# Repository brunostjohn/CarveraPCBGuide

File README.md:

# How to make double-sided PCBs at home with a Carvera (Air)

This is a super in-progress guide for doing this. There's probably many better ways to do this, this is just what's worked for me.

## Table of Contents

- [How to make double-sided PCBs at home with a Carvera (Air)](#how-to-make-double-sided-pcbs-at-home-with-a-carvera-air)
  - [Table of Contents](#table-of-contents)
- [Materials, Tools, and Software](#materials-tools-and-software)
  - [Software](#software)
  - [Materials](#materials)
  - [Tools](#tools)
- [Preparation](#preparation)
  - [Making a PCB-friendly wasteboard.](#making-a-pcb-friendly-wasteboard)
  - [Making sure copper chips aren't fucking with our mill quality.](#making-sure-copper-chips-arent-fucking-with-our-mill-quality)
- [Going from PCB to Gcode.](#going-from-pcb-to-gcode)
  - [Creating your PCB in KiCAD](#creating-your-pcb-in-kicad)
    - [Quick note about text](#quick-note-about-text)
    - [Board setup](#board-setup)
    - [Pre-export work](#pre-export-work)
    - [Actually exporting the damn thing.](#actually-exporting-the-damn-thing)
  - [Importing your PCB to FlatCAM.](#importing-your-pcb-to-flatcam)
    - [Aligning your sides](#aligning-your-sides)
  - [Adding alignment drills.](#adding-alignment-drills)
  - [Actually making gcode for the align drills.](#actually-making-gcode-for-the-align-drills)
    - [Generating g-code for the front side of the PCB.](#generating-g-code-for-the-front-side-of-the-pcb)
  - [Generating g-code for the back side of the PCB.](#generating-g-code-for-the-back-side-of-the-pcb)
  - [Generating gcode for removing the front solder mask.](#generating-gcode-for-removing-the-front-solder-mask)
  - [Generating the gcode for removing the back solder mask.](#generating-the-gcode-for-removing-the-back-solder-mask)
  - [Generating the gcode for lasering on the front silkscreen.](#generating-the-gcode-for-lasering-on-the-front-silkscreen)
  - [Generating the gcode for lasering on the back silkscreen.](#generating-the-gcode-for-lasering-on-the-back-silkscreen)
  - [Generating the gcode for drills and edge cuts.](#generating-the-gcode-for-drills-and-edge-cuts)
- [Milling the board, lasering the board, and other random side quests.](#milling-the-board-lasering-the-board-and-other-random-side-quests)
  - [Attaching the fixture \& adding the fan.](#attaching-the-fixture--adding-the-fan)
  - [Attaching the PCB.](#attaching-the-pcb)
  - [Finding the 0 point and setting up work coordinates.](#finding-the-0-point-and-setting-up-work-coordinates)
  - [Drilling alignment holes.](#drilling-alignment-holes)
  - [Front copper isolation.](#front-copper-isolation)
  - [Front non-copper clearing](#front-non-copper-clearing)
  - [Back copper isoltion \& NCC.](#back-copper-isoltion--ncc)
  - [Applying the back solder mask.](#applying-the-back-solder-mask)

# Materials, Tools, and Software

## Software

- KiCAD
- Makera's CAM
- Fusion 360
- FlatCAM

  This guide uses the 8.994 beta version of FlatCAM. There _will_ be differences between other versions, but the workflow should stay roughly the same.

## Materials

- Copper-clad FR4, duh.
- UV-curable solder mask (both in target solder mask colour and white, you'll see why).
- Some random ass wood for milling the PCB fixture. (should fit on the Carvera bed)
- TPU to make a spindle fan
- Double sided tape.
- An acetate sheet.

## Tools

- The Carvera Air.
- 3D printer (optional)
- A UV light.
- Shop vac (optional)
- The sanding block that came with the Carvera
- Carvera's Laser Module.
- A 0.2mm corn bit/endmill.
- A 2mm/4mm drill bit.
- Makera's solder mask removal bit.
- Corn bits in other various sizes.
- Drill bits also in other various sizes.
- Something to scrape the PCB off the fixture after the double sided tape. I'm using a 3D printer bed scraper.

# Preparation

## Making a PCB-friendly wasteboard.

The MDF wasteboard on the Carvera isn't super friendly to milling PCBs so we need to make our own thing to which we will attach PCBs. Fortunately enough, I've solved this problem already by making a Carvera friendly thing that can accomodate large-ish PCBs and screws into the bed. It isn't entirely my own creation, it's based on [this guide's](https://hackaday.io/project/202478/instructions) fixture created by [Vedran](https://hackaday.io/vedranMv). I only modified it to hold larger PCBs. You don't need to mill all the holes, it's really only the screwholes that matter. Here's a photo of mine.

I made it out of some random wood my landlord had in her shed. Just make if flat enough and you'll be fine.

You can get the [Fusion project here](./projects_and_gcode/fusion/PCB%20fixture%20thing.f3d) or the [STEP file here](./projects_and_gcode/step/PCB%20fixture%20thing.step).

## Making sure copper chips aren't fucking with our mill quality.

When the bit you're using mills it's own chips (or in this case, dust), you get more burrs and more bullshit. To prevent this you can either use a vaccuum attached to your Carvera or a delightful fan.

[RedGT500](https://www.printables.com/@RedGT500_1977691) has already made a great fix to this. A 3D printable fan made out of TPU that's made to go on your spindle. You can even see mine in that photo of the fixture above. You can download it [here](https://www.printables.com/model/1332188-carvera-spindle-fan-beefy-version/files). I've also reuploaded it [here](./projects_and_gcode/step/Spindle%20Fan.step) to protect against link rot.

# Going from PCB to Gcode.

## Creating your PCB in KiCAD

Teaching you to actually make PCBs is outside the scope of this guide. God knows I know fuck all about making PCBs or CNC. What I do know is how I made my PCB so that it works with this process.

This doesn't affect making your schematic, so I'm gonna skip right over to the PCB editor.

### Quick note about text

First, if you think any text you make is gonna look fine, you're sorely mistaken. Don't even bother. Hide all the text and make sure it doesn't end up in the final exports.

### Board setup

Let's move onto the money shot.

- The minimum clearance between tracks should be 0.2mm (you _can_ set 0.1mm and have good results but you have to mind yourself so you don't get the tracks too close together, this is relevant for some smaller ICs or USB-C ports).
- The minimum track width should be 0.2mm (NOT any lower unless you have tiny ass bits, which I don't and haven't tested).
- Your minimum via diameter should be 0.9mm (so that you can drill 0.6mm holes for them). Smaller vias will be a pain in the ass, don't even bother with them.
- Your copper to hole clearance should be 0.25mm. You can go lower (as low as 0.2mm), but I wouldn't recommend it.
- Your copper to edge clearance should be 0mm. This way KiCAD won't force FlatCAM to mill the shit out of the boards edges wasting your time and bit life.
- Your minimum through-hole should be 0.3mm (or the smallest bit you've got).
- Your hole to hole clearance should be 0.2-0.25mm.

### Pre-export work

To make our board show up consistently in the right spot in all of the pieces of software we'll be using, you gotta set a grid & drill/place origin.

In KiCAD's PCB editor, select the `Grid Origin` option.

Then, place it at the bottom left corner of your board.

Now, press and hold the grid origin button until a second option pops out.

That's the drill origin button. Click on that and place it in the same spot as the grid origin.

You are now ready to export your board.

### Actually exporting the damn thing.

Click on `File > Fabrication Outputs > Gerbers`.

Now, select the output folder, select your layers, select `Use drill/place file origin`. First, click on `Generate Drill Files` and also select `Drill Origin > Drill/place file origin`, then click on `Generate Drill File` and close. Then, click on `Plot`. Your board should now have the required outputs to be milled in the folder you selected.

(I've taken this photo from [Vedran's guide](https://hackaday.io/project/202478/instructions) because I'm on macOS Tahoe and KiCAD's export window is freaking OUT on it)

You should now have the Gerbers you need to mill your board.

## Importing your PCB to FlatCAM.

Open up FlatCAM and click on `File`. Then hover over `Open` and select `Open Gerber`. **ONLY** import your front and back copper layers. Don't import anything else.

You should see your board on the newly opened side panel:

To make seeing them a little bit easier, feel free to select whatever colours you think they should have:

Having done that, you should see something like this:

### Aligning your sides

It may seem like the boards are in the right orientation, but that is not the case. Remember, this is a 2D program and if you flip over the board, you will notice that it's almost as if it's _mirrored_. Let's fix that.

At the top of the UI, click on `Tool` and select `2-Sided PCB`:

This will take you to a panel that looks something like this:

First, as the source object, select the _back side of the board_. I know that that's confusing, but this is the object that will end up getting mirrored. Horrible naming, but we can work with that.

Let's now mirror our back side. in the Mirror Operation section of the 2-Sided PCB panel, select the X axis for your mirror operation (we'll be flipping the board over on its long side) and select Box as your reference. I've seen a YouTuber use Point and do some crazy ass math, but that's quite silly considering we're on a computer that can _compute_ it for us.

Next, as your reference object, select the front side of your board. If you've done this right, your Mirror Operation panel should look something like this:

Looks great! Let's press Mirror to get it onto the right side. Things will feel a bit wrong now. If you've done this right, this is what it should look like:

This seems wrong because our vias are not aligned. Remember, this is _Flat_ CAM. So what is happening here instead is that we're looking at our boards from the _top_, just like our CNC will. This means that if you physically flip over your soon-to-be board, you will see the same view as you are right now in FlatCAM.

## Adding alignment drills.

We're almost done with the 2-Sided PCB tool. All we need to do now, is make sure that we can somehow reliably align both sides on our CNC's work area. If you've ever done this manually, you'll know that it's basically impossible.

In the PCB Alignment section, set your drill diameter to the size of your alignment pins. I'm using the 2mm diameter dowel pins that came with the PCB fabrication toolkit, but you can use 4mm if you haven't bought it and are using the slightly larger pins that come with the machine itself.

To do this accurately, we need to do some math.

Let's figure out where our alignment pins should be. Go back to the project tab in FlatCAM and find the front side of your board. Right click on it and select `Properties`.

In there, you will see a dimensions section. This contains what we're looking for, the **Length** and **Width** of the board:

Make note of these and go back to the 2-Sided PCB tool like shown before.

In the PCB Alignment section, there will be a text field titled `Alignment Drill Coordinates`. We're calculating these because it's gonna be hard to get this right manually.

We want 4 drills on opposite corners of the board 3mm away from the board itself.

So what we want is:

- **A hole on the bottom left.**
  In my case, it's at `(0.0, -3.0)` because we're to the leftmost corner of the board, 3mm away from the bottom edge.
- **A hole on the top left.**
  In my case, that's `(0.0, 25.669)` because I want it on the same "line" as the left edge but 4mm away from the top edge (so $22.669+3=25.669$).
- **A hole on the bottom right.**
  In my case, that's at `(51.024, -3)` because we're at the rightmost corner of the board, 3mm away from the bottom edge.
- **A hole on the top right.**
  For me, that's at `(51.024, 25.669)` because I want it on the same "line" as the right edge but 4mm away from the top edge (so $22.669+3=25.669$).

This, in aggregate, is:
```(0.0000, -3.0000),(51.0240,-3),(0, 25.6690),(51.0240,25.6690)```

Let's punch these numbers into FlatCAM and click on `Create Excellon Object`.

You should now see your alignment drills on the Plot Area.

## Actually making gcode for the align drills.

I don't trust FlatCAM with doing these drilling ops. Partly because I'm not super familiar with it and partly because MakeraCAM makes it dead easy. Let's open up a new 3-axis project in MakeraCAM.

Now, set up your stock. Pick the PCB material and set the XYZ values to anything that fits with your board.

Now we're ready to drill some shit. Let's export our fresh Excellon drills from FlatCAM.

Save them somewhere they won't get lost and get back to MakeraCAM. In the layer panel, right click 2D layers and select `Import Graphic > Import PCB`.

Once you import your drills, you should be able to see them in the layers panel and in the work area. Don't worry if the size is slightly wrong, that's okay.

You'll also notice that they go outside of the "work area". **Don't move them by even a millimetre**. Just leave them as-is. This is fine and will be rectified later when we go to drill them.

Select all your drills by using MakeraCAM's `Select Graphics` options:

You should see them all get kind of dashy. With them selected, go into 2D toolpaths and select 2D drilling.

Let's sort out the settings. I'm using my 2mm drill. I used a clearance height of 5mm because there's nothing in the way of the toolhead as these drills are being created. Use feeds & speeds for PCBs. Your wooden base and bit will be fine (I think?). We're drilling 6mm down because the dowel pins are about 10mm in height, and we want them to be secure.

That's it! You're now ready to drill your alignment drills. Let's move onto generating the gcode for our top and bottom layers.

### Generating g-code for the front side of the PCB.

Let's go back to FlatCAM. Double click on the front layer of your PCB. That should bring you to this panel:

We will start by electrically isolating your traces. This removes material around only the traces. Click on `Isolation Routing`. You will now see a different panel:

We will lie about our bits diameter. This is so that FlatCAM actually mills them. Your tool's supposed to be smaller than your traces. But it's fine if it's equal to their width. So fuck it, let's lie. It _does_ work. Double click what's currently in there and type in 0.19. This will make some of your traces slightly undersized. For me, that's worked out okay but YMMV. Then select the tool type. We're using a corn bit so any of the CX options are fine. Let's pick C1 for the vibes.

Now, right at the bottom, click on `Generate Geometry`. This will create geometry for us that we can later use to CNC the board.

You will see a bunch of toolpath parameters. In the path type, select `Iso`:

I'm setting my cut Z to -0.05. That's enough to get the copper off the board and get to the FR4 for me. Things might be different for you, so experimentation is king here. I'm using an XY feedrate of 120 and Z feedrate of 60. These tools are mad fragile so it's better to not fuck about. I'm also using a spindle speed of 15k because I've gotten the best results that way.

When you're done, click on `Generate CNCJob object`. This will generate actual gcode we can use. You will now see an actual toolpath forming. The panel will also give you an option to save your gcode. Do that and open the generated file in Notepad.

For the gcode-inclined among us, you'll notice that T1 and M6 are on separate lines:

This makes the Carvera very angry. It stops the job and loses its heightmap. It's a nice machine so let's not make it angry. Delete the newline between these, add a space, and save. Here's what a fixed file looks like:

You'll need to do this for every CNCJob you save from FlatCAM. There's probably a fix for this. I haven't found it yet.

Let's now get back to the Project tab in FlatCAM. Double click on your front layer again. This will open up the Gerber Object panel again. This time, click on NCC Tool. That is the **n**on-**c**opper **c**leaning tool. Once again select the C1 tool type and a diameter of 0.19. Generate your geometry. Now, sometimes, that takes ages. Let it cook. It might complain that it couldn't fully isolate.

Sometimes it might even tell you where the polygons it failed to clear are. Double check that everything is still fine. It probably is.

Once you do, configure your toolpath. Most, if not all, of the settings will be the same as for isolating traces.

Once you're satisfied, click on the `Generate CNCJob object button`. Verify your toolpath and save your CNC code. Repeat the same steps as for the isolation gcode where we had to remove a newline from there.

## Generating g-code for the back side of the PCB.

Repeat the steps you did for the front side, just for the back side this time.

We're now officialy done with FlatCAM. We don't need to look at it again (yay!).

## Generating gcode for removing the front solder mask.

Let's open up a new 3-axis project in MakeraCAM.

Now, set up your stock. Pick the PCB material and set the XYZ values to anything that fits with your board.

In the layer panel, right click 2D layers and select `Import Graphic > Import PCB`.

Select your _front copper layer_. I know you'll be tempted to use the solder mask gerber. Because the solder mask gerber won't remove mask from the vias, It's not particularly useful to us.

Once you import your layer, it should look something like this:

You'll notice MakeraCAM helpfully created a pad layer for us. That's what we'll be primarily working with. Let's hide the non-pad layer.

Right click on your pad layer and click on `Select graphics` to select all our pads & vias.

With that selected, select the 2D Pocket toolpath from the 2D options.

For this pocket, we are using the solder mask removal tool.

We're using a taller clearance height to avoid fucking the tool into our dowel pins. An end depth of 0.3mm has delivered solid results to me, but in the worst case one can re-run the toolpath with a higher depth. Anyways, let's run calculate.

Great! It seems like everything was calculated. Wait, not everything. Some of the pads are too small!

Don't worry, I have a trash quality solution to this that works unnecessarily well.

Start by holding down `Shift` and left clicking on pads that weren't generated. Group this by the _size of the pad_. So for example, I'm not gonna do the RP2040 pads because they're small as fuck. We'll start with the NOR flash:

Now, let's create a new pocket toolpath. Same settings as before with one change. We will use the offset option.

This will force MakeraCAM to generate a toolpath by making it pretend our selected graphic is larger than it actually is. This _does_ make pads slightly larger than they should be. But in reality, with our NCC toolpaths and solder mask spread, this usually means that the extra removed soldermask is still kind of there because it goes deeper than the tool does. You'll see that in a photo later.

Now, let's do the RP2040 pads (as an example of some smaller pads). let's start with the ones oriented horizontally. Do the same offset trick. Here's where it gets funky. These pads are small as shit so ripping them off is SUPER easy. You want to _minimise the amount of time the tool spends on the pad_. And also, you want to minimise the pad itself. So experiment until you find the smallest possible offset that makes the machine mill the pads.

This will take experimentation. Take your time with it. Do the same for the vertical pads now.

When you're done, your Carvera should have toolpaths for all your pads.

Export your gcode and save for later.

## Generating the gcode for removing the back solder mask.

Take your mirrored back board from FlatCAM and export the Gerber. Import to MakeraCAM and mirror it vertically:

## Generating the gcode for lasering on the front silkscreen.

Let's open up a new 3-axis project in MakeraCAM.

Now, set up your stock. Pick the PCB material and set the XYZ values to anything that fits with your board.

In the layer panel, right click 2D layers and select `Import Graphic > Import PCB`.

Import your front silkscreen layer.

Any text you have needs to go. I haven't figured out how to make it legible yet but it'll legitimately look like trash.

Just delete it.

Now, this part you can only do after experimenting a little bit. The laser is _very_ slightly off from where the mill ends up. This will cause your silkscreen to be off. I still haven't gotten the right offsets, but here's how to apply them.

Right click your silkscreen layer in the layers section of MakeraCAM and click on `Select Graphics`.

Now, click on the transform menu and select `Move`.

You will be brought to a delightful panel for moving shit. It'll tell you your current selection's location:

Now, my last proof board turned out like this:

It looks like on the X axis we are too far to the right (so, we need to compensate by subtracting) and on the Y axis we are too far to the bottom (so we need to compensate by adding).

I'm gonna try -0.75mm on the X axis and +0.3mm on the Y axis.

Based on the values in the move panel:

- X axis
  $24.579-0.75=23.829$
- Y axis
  $11.161+0.3=11.461$

Let's type that into MakeraCAM.

Great, with our paths translated we're ready to create our laser toolpaths.

Now, this is very important, **select things by their thickness**. Group things as thick as each other together. This way, you can get a result that doesn't look like shit.

In my case, there's only a few tiny bits that have the same thickness. Let's select everything else for now.

From the laser toolpaths dropdown, select Laser Vector.

As for settings, set speed at a hilariously low 30mm/min and power at 3%. We're not actually trying to engrave or cut anything (you'll see when we actually run the toolpaths), we're exploiting the laser's wavelength to use it to selectively cure the white soldermask. Set the indent distance at _the lowest possible value that still generates a complete toolpath_. Pair that with using the laser in line mode. The thinnest laser path can generate the thickest solder mask, so it's better to err on the cautious side.

Now, thing by thing generate your thicker paths with the appropriate indent distances. The thicker it is, the higher the indent distance should be.

With all the toolpaths done, you can now export your gcode and stash it for later.

## Generating the gcode for lasering on the back silkscreen.

About the same as the front silkscreen. Just with the caveat that you have to mirror it vertically as shown in the previous sections.

## Generating the gcode for drills and edge cuts.

This will be the last toolpath for our PCB.

Let's open up a new 3-axis project in MakeraCAM.

Now, set up your stock. Pick the PCB material and set the XYZ values to anything that fits with your board.

In the layer panel, right click 2D layers and select `Import Graphic > Import PCB`.

Import your PTH, NPTH, and edge cut layers.

For creating drill holes, there are 2 strategies. You can use a 2D Pocket toolpath or a 2D Drill toolpath. The drill toolpath is greatly preferred because it risks your pads less. If you don't have the right sized drills though, you can make do with a pocket and very often your PCB will be okay. We will use both strategies here because it's fun.

Let's start by using plain ol' drills. Right click the layer that has the right sized drills for your bits and click on `Select Graphics`.

Now, select the 2D Drilling toolpath from the 2D toolpaths dropdown.

As for the settings, you want to drill 1.6mm down to ensure you go fully through the board. This will make a delightful hole in your wooden block. That's fine because the bit should survive this blunder. Remember to use a drill that matches your layer drill size.

Now, let's do the pleb way of drilling a hole - the 2D pocket toolpath. Select the drills you don't have the proper bits for and select 2D Pocket from the 2D toolpaths dropdown.

Select a corn bit smaller than your smallest drill size. Make it mill 1.6mm down to make sure we get all of the board.

For the strategy, we're doing outside in. I've gotten the best results with that.

Almost done with our last toolpath! Let's cut the board out of the stock. Now, edge cuts are sneaky little shits. It doesn't look like it, but there's two of them. Zoom in and delete the smaller one.

Select your edge cut (NOT cuts!) and select the 2D Contour toolpath from the 2D toolpaths dropdown.

For these, use your _biggest_ corn bit. Otherwise, it'll look like shit. Again, cutting 1.6mm down.

To not end up fucking our board, pick the outside strategy.

Last one, so the board doesnt go flying out of the FR4, add some tabs. Click on custom, make them triangle shaped, and select `Add`.

Now, click roughly in the centre of each edge of the contour.

Sick. Now press `Exit Add` and calculate your toolpath.

You can now export your g-code. Since we're using many corn bits, MakeraCAM will complain about tool numbers. Change them up until you're happy with the numbers. Just make each tool have a different one.

With your g-code exported, you're now ready to mill some shit. Let's get to making everything.

# Milling the board, lasering the board, and other random side quests.

## Attaching the fixture & adding the fan.

Let's get started by screwing in the fixture and adding the fan. Take anything in the spindle out of the spindle and press fit the fan. After that, reference the photo below to see where the fixture screws in. Use the medium-long screws that come with the Carvera.

## Attaching the PCB.

Put double sided tape all over the back of the PCB.

Then, stick it on the fixture. Avoid putting any drills around the screws at the bottom of the fixture. Make sure there's enough space to flip the board over while keeping the entirety of it on the fixture itself.

Feel free to use the roller from the PCB fabrication kit (if you bought it) to ensure the adhesive is nice and squished.

## Finding the 0 point and setting up work coordinates.

Insert the leveling probe into the spindle.

Let's open up the Carvera Controller. Connect to the machine and click on the top right button. Then, select the device diagnose menu. In there, turn on the probe laser.

You will see the laser come alive. Now, exit the diagnose menu and go into the manual control menu.

Here, move the toolhead until the laser pointer is pointing at where you want the X and Y zero points to be (where the PCB starts). Remember that some of the align holes are at minus points when doing this. If you feel like things are moving too slow or too fast, change how fast the Carvera moves the axes.

Find your zero point.

Once you're happy with the zero point, let's start running the alignment hole job.

## Drilling alignment holes.

When you click on start job, you will see a work origin and leveling menu. Your toolhead is at the X and Y zero point right now. Let's let the machine know about that by clicking `Config` under `Set Work Origin` and setting the anchor as `Current Pos`.

Let's move onto leveling. You don't need to go super crazy here, the drills just need to be accurate enough.

Let's start our job and wait until it's done.

Okay, there's holes now! Get rid of the debris using a vacuum.

After you've cleared them, put the dowel pins in. From now on, **anytime you're machining the board the dowel pins should be in it**. That will prevent unnecessary movement and ensure alignment.

## Front copper isolation.

Let's move onto the fun stuff. Load up the copper isolation job.

**DO NOT** change the work origin settings. These will now stay the same for the entire duration of us milling this board.

We will change the levelling settings though. We want to be absolutely certain we have all the weird imperfections accounted for. Use 15 levelling points. Yeah, it's a lot. Yeah, it'll take ages. And yeah, it's worth it.

Great! Let's wait for our machine to be done.

Nice result!

## Front non-copper clearing

Let's now move onto milling out the non-copper sections. Load up the NCC job.

Now, before you run it, **DO NOT** enable any option that requires the probe. We want the Carvera to reuse it's heightmap. Doing that will cause it to clear it and you'll get worse results.

Let's wait for NCC to be done.

## Back copper isoltion & NCC.

With front NCC done, we can scrape the board off our fixture. Add double sided tape _only above and below the board_. If you add tape onto the board, you run the risk of scraping traces.

Just like with the front side, run maximum leveling (15 points) and start the isolation job. Once done, start NCC without using the probe. Once that's done, we're ready to move onto solder mask.

## Applying the back solder mask.

Right now, the board will have a bunch of burrs. We don't want that as it will cause an uneven stick & coat for the UV-curing solder mask. Fortunately, Makera includes a fine enough sanding block with the Carvera.

Rub that shit on the board until it gets nice and shiny.

Now, the sander itself leaves some nasty shit on the board. Grab some isopropanol and swab it off.

As you can see, that is quite nasty.

Okay, grab your favourite solder mask.

Apply it evenly-ish on the board.

Now, grab a transparent sheet. I'm using some random acetate sheets I had at home.

Squish it on the board.

Now, use the roller that comes in the PCB fabrication kit (or a credit card) to get the solder mask spread evenly (enough) on the board.

Once you're done, you should be left with something that looks kind of like this.

Now, grab your favourite UV light, set it to at least 15 minutes, and start curing this thing.

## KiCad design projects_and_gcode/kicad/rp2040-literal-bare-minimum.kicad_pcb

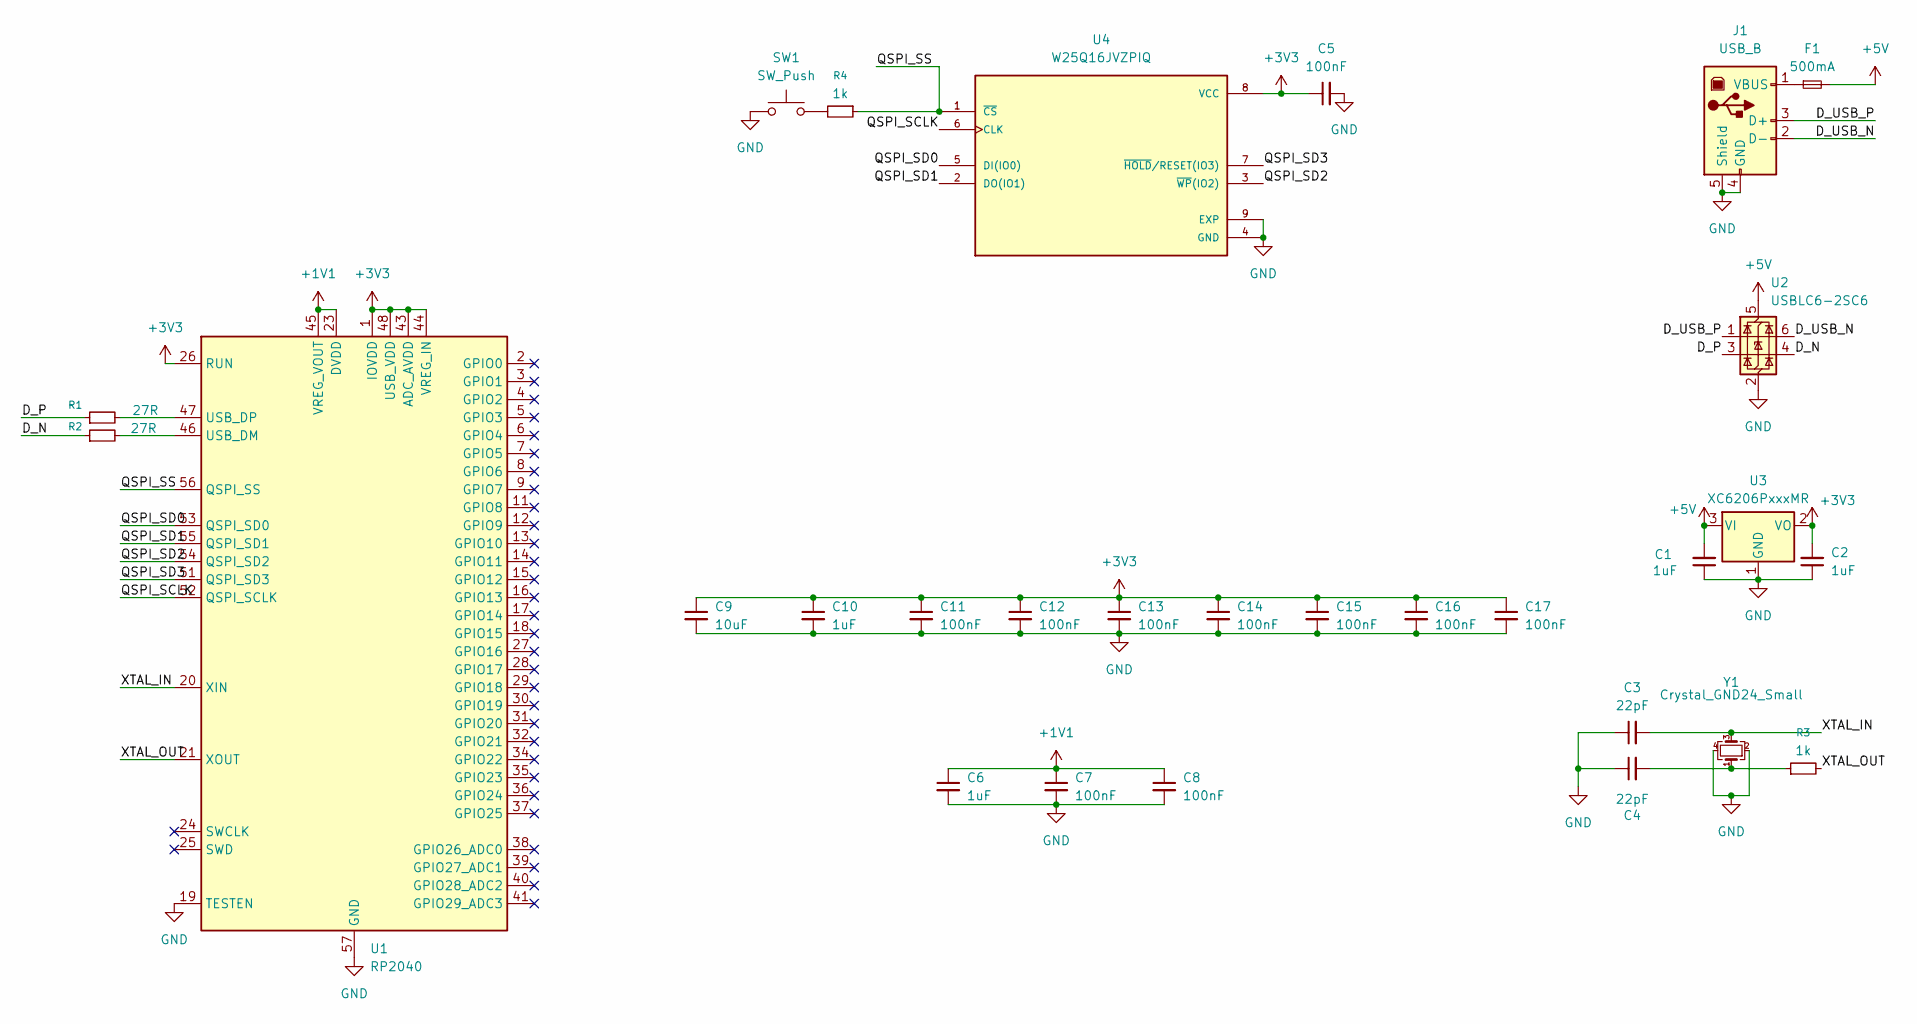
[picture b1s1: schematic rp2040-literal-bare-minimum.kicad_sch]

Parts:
C1, C2, C6, C10: 1uF; C_0402_1005Metric-notxt
C3, C4: 22pF; C_0402_1005Metric-notxt
C5, C7, C8, C11, C12, C13, C14, C15, C16, C17: 100nF; C_0402_1005Metric-notxt
C9: 10uF; C_0402_1005Metric-notxt
F1: 500mA; Fuse_1206_3216Metric-notxt
J1: USB_B; USB_B_Lumberg_2411_02_Horizontal-notxt
R1, R2: 27R; R_0402_1005Metric-notext
R3, R4: 1k; R_0402_1005Metric-notext
SW1: SW_Push; SW_SPST_EVQP2-notxt
U1: RP2040; QFN-56-1EP_7x7mm_P0.4mm_EP3.2x3.2mm
U2: USBLC6-2SC6; SOT-23-6
U3: XC6206PxxxMR; SOT-23-3
U4: W25Q16JVZPIQ; SON127P500X600X80-9N
Y1: Crystal_GND24_Small; Crystal_SMD_3225-4Pin_3.2x2.5mm-notxt

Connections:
+1V1: C6.1, C7.1, C8.1, U1.23 (DVDD), U1.45 (VREG_VOUT), U1.50 (DVDD)
+3V3: C2.2, C5.1, C9.1, C10.1, C11.1, C12.1, C13.1, C14.1, C15.1, C16.1, C17.1, U1.1 (IOVDD), U1.10 (IOVDD), U1.22 (IOVDD), U1.26 (RUN), U1.33 (IOVDD), U1.42 (IOVDD), U1.43 (ADC_AVDD), U1.44 (VREG_IN), U1.48 (USB_VDD), U1.49 (IOVDD), U3.2 (VO), U4.8 (VCC)
+5V: C1.2, F1.2, U2.5 (VBUS), U3.3 (VI)
/D_N: R2.1, U2.4 (I/O2)
/D_P: R1.1, U2.3 (I/O2)
/D_USB_N: J1.2 (D-), U2.6 (I/O1)
/D_USB_P: J1.3 (D+), U2.1 (I/O1)
/QSPI_SCLK: U1.52 (QSPI_SCLK), U4.6 (CLK)
/QSPI_SD0: U1.53 (QSPI_SD0), U4.5 (DI(IO0))
/QSPI_SD1: U1.55 (QSPI_SD1), U4.2 (DO(IO1))
/QSPI_SD2: U1.54 (QSPI_SD2), U4.3 (~WP(IO2))
/QSPI_SD3: U1.51 (QSPI_SD3), U4.7 (~HOLD/RESET(IO3))
/QSPI_SS: R4.1, U1.56 (QSPI_SS), U4.1 (~CS)
/XTAL_IN: C3.2, U1.20 (XIN), Y1.3
/XTAL_OUT: R3.2, U1.21 (XOUT)
GND: C1.1, C2.1, C3.1, C4.1, C5.2, C6.2, C7.2, C8.2, C9.2, C10.2, C11.2, C12.2, C13.2, C14.2, C15.2, C16.2, C17.2, J1.4 (GND), J1.5 (Shield), SW1.1, U1.19 (TESTEN), U1.57 (GND), U2.2 (GND), U3.1 (GND), U4.4 (GND), U4.9 (EXP), Y1.2, Y1.4
unnamed: C4.2, R3.1, Y1.1
unnamed: F1.1, J1.1 (VBUS)
unnamed: R4.2, SW1.2
unnamed: R2.2, U1.46 (USB_DM)
unnamed: R1.2, U1.47 (USB_DP)

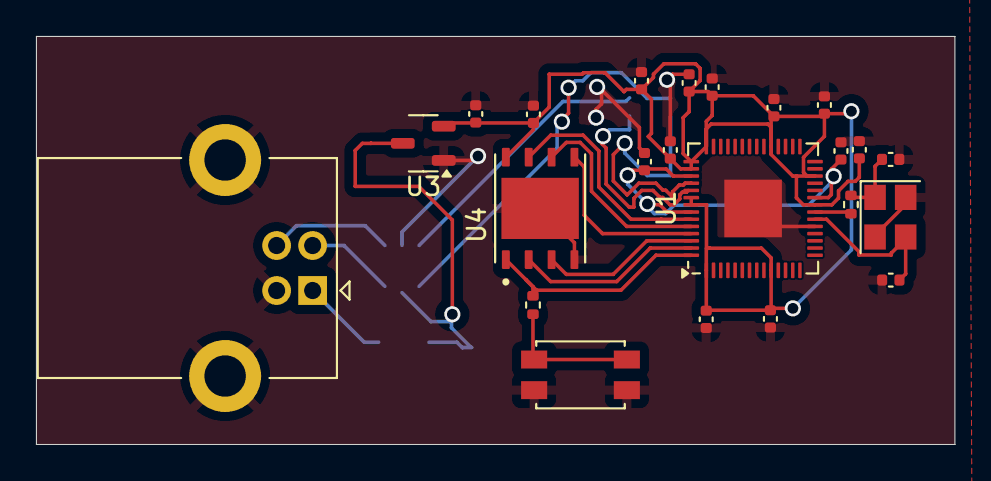
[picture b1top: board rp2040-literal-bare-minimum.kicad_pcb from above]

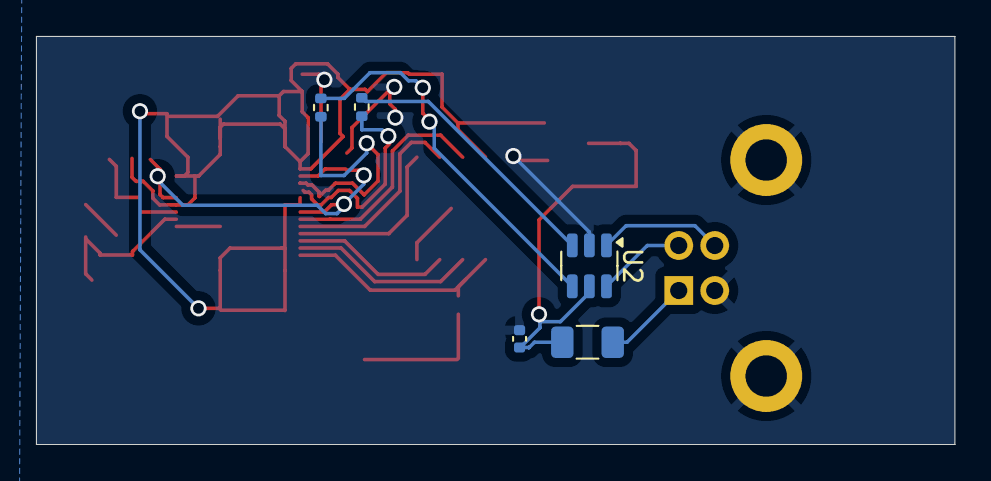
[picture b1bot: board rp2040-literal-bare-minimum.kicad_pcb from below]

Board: 2 copper layers, 51.0 x 22.7 mm, 28 parts (5 on the bottom side), 21 nets.

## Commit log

2025-07-27 init
2025-07-27 that looks trash
2025-07-27 lotta cad shit
2025-07-27 the software side is done, gotta do the actual milling side now
2025-07-27 overshare
2025-07-27 start applied carvera shit
2025-07-27 update ncc pic
2025-07-27 we need a toc
2025-07-28 moar
2025-07-28 clean up da list
2025-07-28 chill
2025-07-28 rolled
2025-07-28 mirror vertically
2025-07-28 mirror vertically ok
